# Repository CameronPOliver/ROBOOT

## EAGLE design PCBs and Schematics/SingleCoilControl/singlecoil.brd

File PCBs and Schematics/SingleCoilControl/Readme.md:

Schematic, PCB and gerber files for a board controlling a single coil charge/discharge

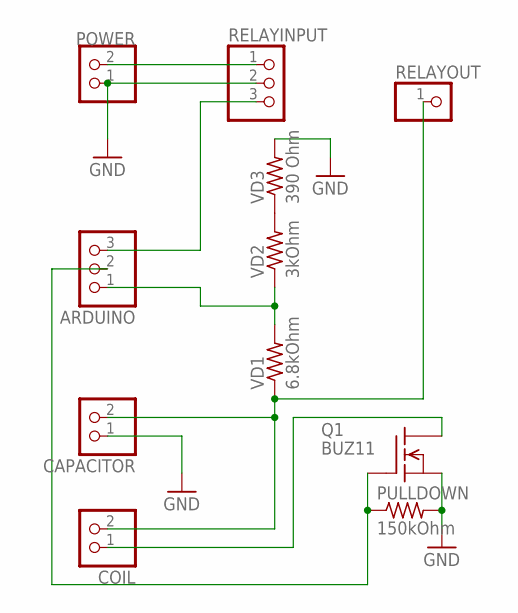
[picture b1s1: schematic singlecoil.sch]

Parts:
ARDUINO: PINHD-1X3; 1X03
CAPACITOR: PINHD-1X2; 1X02
COIL: PINHD-1X2; 1X02
POWER: PINHD-1X2; 1X02
PULLDOWN: 150kOhm; 0204V
Q1: BUZ11; TO220
RELAYINPUT: PINHD-1X3; 1X03
RELAYOUT: PINHD-1X1; 1X01
VD1: 6.8kOhm; 0204V
VD2: 3kOhm; 0204V
VD3: 390 Ohm; 0204V

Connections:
GND: CAPACITOR.1, POWER.1, PULLDOWN.2, Q1.3 (S), RELAYINPUT.2, VD3.2
unnamed: POWER.2, RELAYINPUT.1
unnamed: ARDUINO.1, VD1.2, VD2.1
unnamed: ARDUINO.2, PULLDOWN.1, Q1.1 (G)
unnamed: COIL.1, Q1.2 (D)
unnamed: VD2.2, VD3.1
unnamed: ARDUINO.3, RELAYINPUT.3
unnamed: CAPACITOR.2, COIL.2, RELAYOUT.1, VD1.1

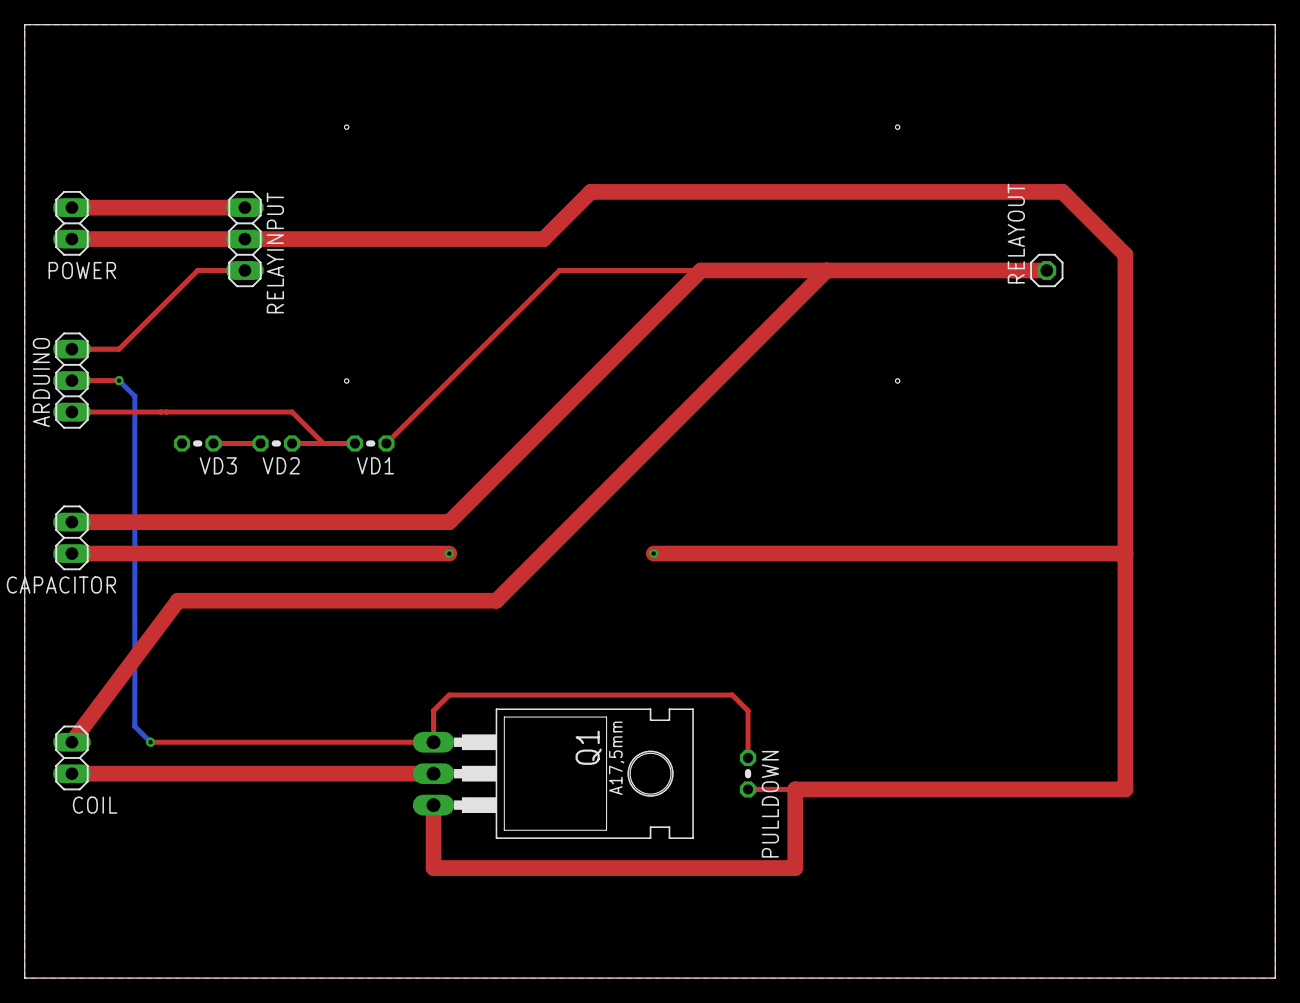
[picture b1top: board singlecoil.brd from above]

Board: 2 copper layers, 101.0 x 77.0 mm, 11 parts (0 on the bottom side), 8 nets.

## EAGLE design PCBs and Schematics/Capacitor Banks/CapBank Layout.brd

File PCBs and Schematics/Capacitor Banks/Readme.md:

Schematic, PCB, and gerber files for the capacitor bank PCB

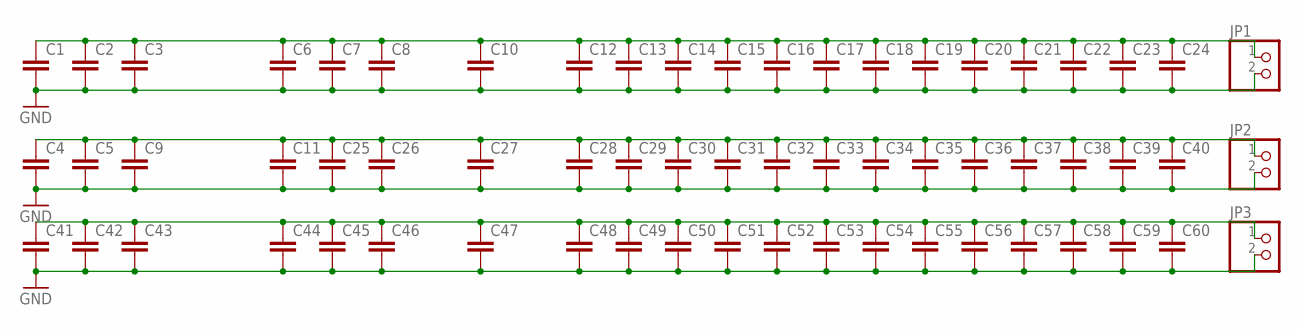
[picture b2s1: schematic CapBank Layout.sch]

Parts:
C1, C2, C3, C4, C5, C6, C7, C8, C9, C10, C11, C12, C13, C14, C15, C16, C17, C18, C19, C20, C21, C22, C23, C24, C25, C26, C27, C28, C29, C30, C31, C32, C33, C34, C35, C36, C37, C38, C39, C40, C41, C42, C43, C44, C45, C46, C47, C48, C49, C50, C51, C52, C53, C54, C55, C56, C57, C58, C59, C60: C5/5; C5B5
JP1, JP2, JP3: PINHD-1X2/90; 1X02/90

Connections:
GND: C1.2, C2.2, C3.2, C4.2, C5.2, C6.2, C7.2, C8.2, C9.2, C10.2, C11.2, C12.2, C13.2, C14.2, C15.2, C16.2, C17.2, C18.2, C19.2, C20.2, C21.2, C22.2, C23.2, C24.2, C25.2, C26.2, C27.2, C28.2, C29.2, C30.2, C31.2, C32.2, C33.2, C34.2, C35.2, C36.2, C37.2, C38.2, C39.2, C40.2, C41.2, C42.2, C43.2, C44.2, C45.2, C46.2, C47.2, C48.2, C49.2, C50.2, C51.2, C52.2, C53.2, C54.2, C55.2, C56.2, C57.2, C58.2, C59.2, C60.2, JP1.2, JP2.2, JP3.2
unnamed: C1.1, C2.1, C3.1, C6.1, C7.1, C8.1, C10.1, C12.1, C13.1, C14.1, C15.1, C16.1, C17.1, C18.1, C19.1, C20.1, C21.1, C22.1, C23.1, C24.1, JP1.1
unnamed: C4.1, C5.1, C9.1, C11.1, C25.1, C26.1, C27.1, C28.1, C29.1, C30.1, C31.1, C32.1, C33.1, C34.1, C35.1, C36.1, C37.1, C38.1, C39.1, C40.1, JP2.1
unnamed: C41.1, C42.1, C43.1, C44.1, C45.1, C46.1, C47.1, C48.1, C49.1, C50.1, C51.1, C52.1, C53.1, C54.1, C55.1, C56.1, C57.1, C58.1, C59.1, C60.1, JP3.1

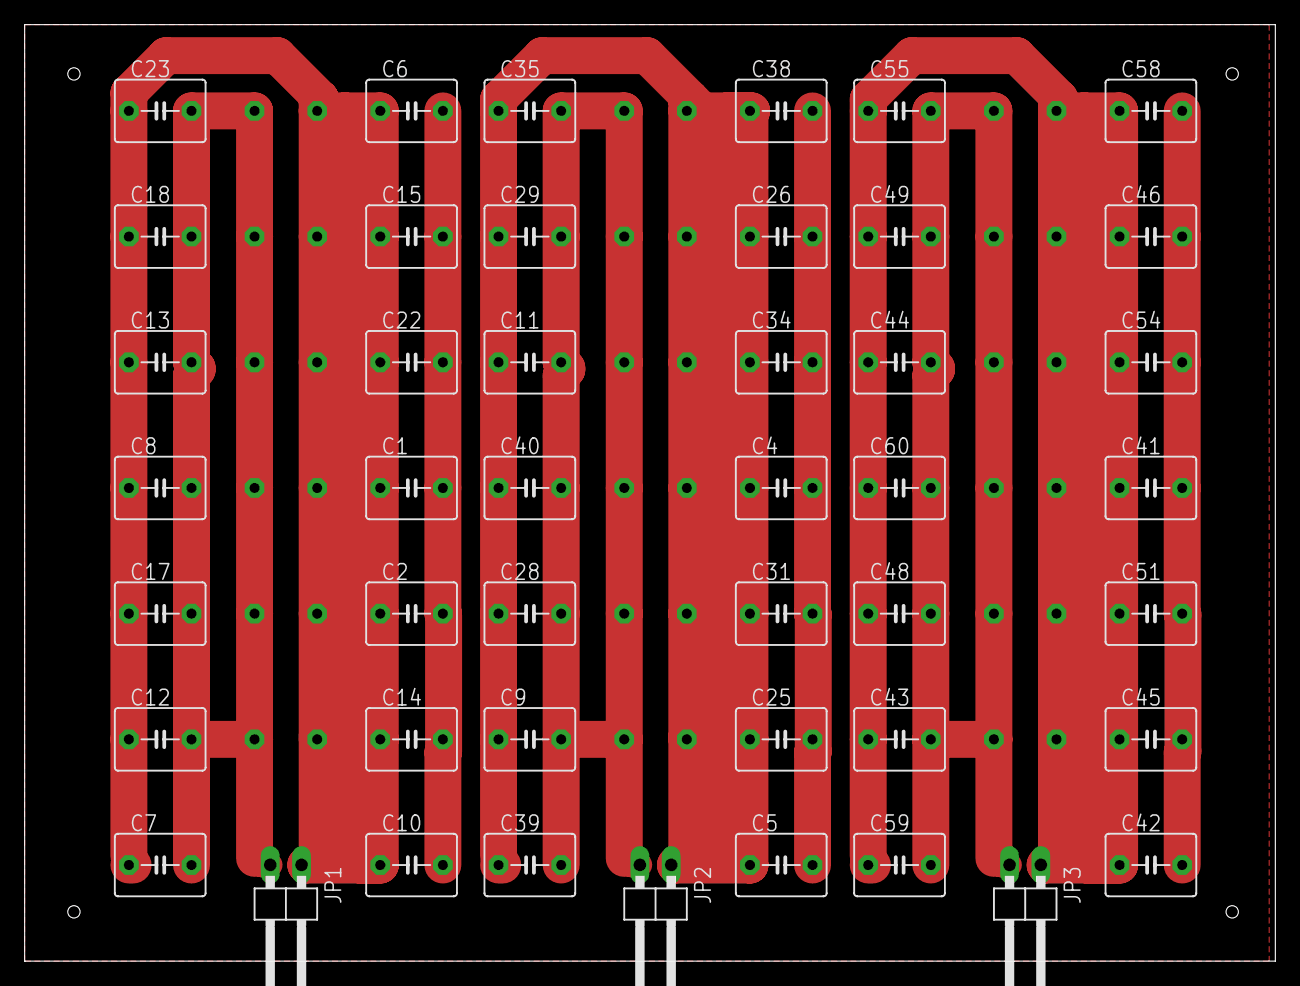
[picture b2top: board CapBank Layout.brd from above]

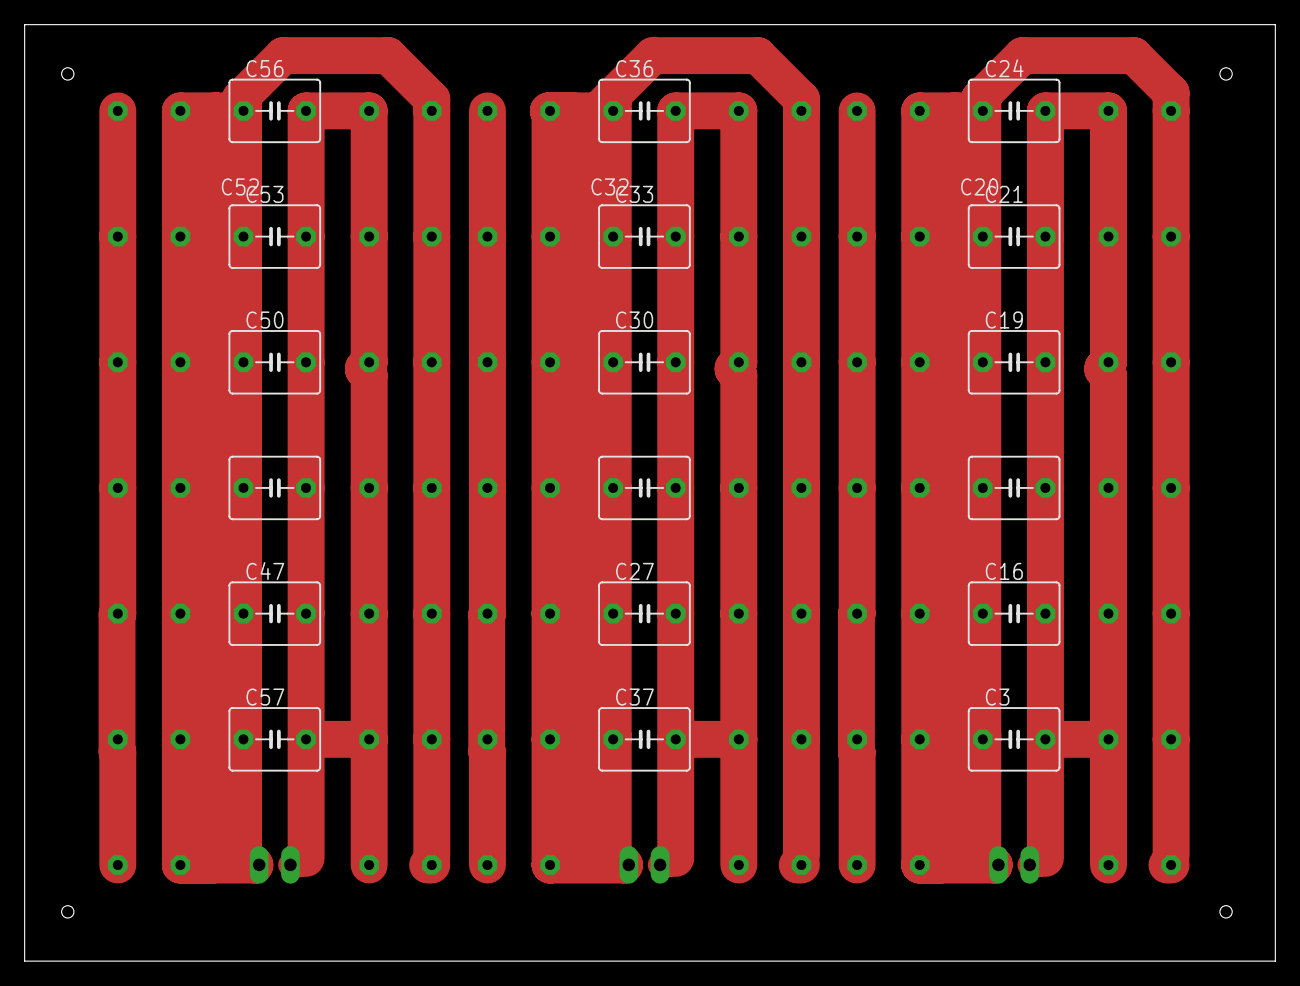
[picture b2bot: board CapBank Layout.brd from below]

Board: 2 copper layers, 101.5 x 76.0 mm, 63 parts (18 on the bottom side), 4 nets.

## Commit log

2019-11-12 Add files via upload
    Test code for initiating capacitor charge and discharge sequences by with tactile buttons.
    In this version there are 2 buttons and a potentiometer:
    -Charge Button: Should act as a flip-flop (when pressed, the charging pin output signal will turn on and remain on until pressed again to turn off and remain off, and so on).
    -Discharge Button: Should initiate a 2 pin discharge sequence (when pressed, the coil 1 discharge signal pin should turn on for a set amount of time, then turn off, followed by a set delay period, th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
    -Potentiometer: Can be used to vary the discharge times and delays (currently the discharge dela
2019-11-15 Add files via upload
    First Schematic of the coilgun
